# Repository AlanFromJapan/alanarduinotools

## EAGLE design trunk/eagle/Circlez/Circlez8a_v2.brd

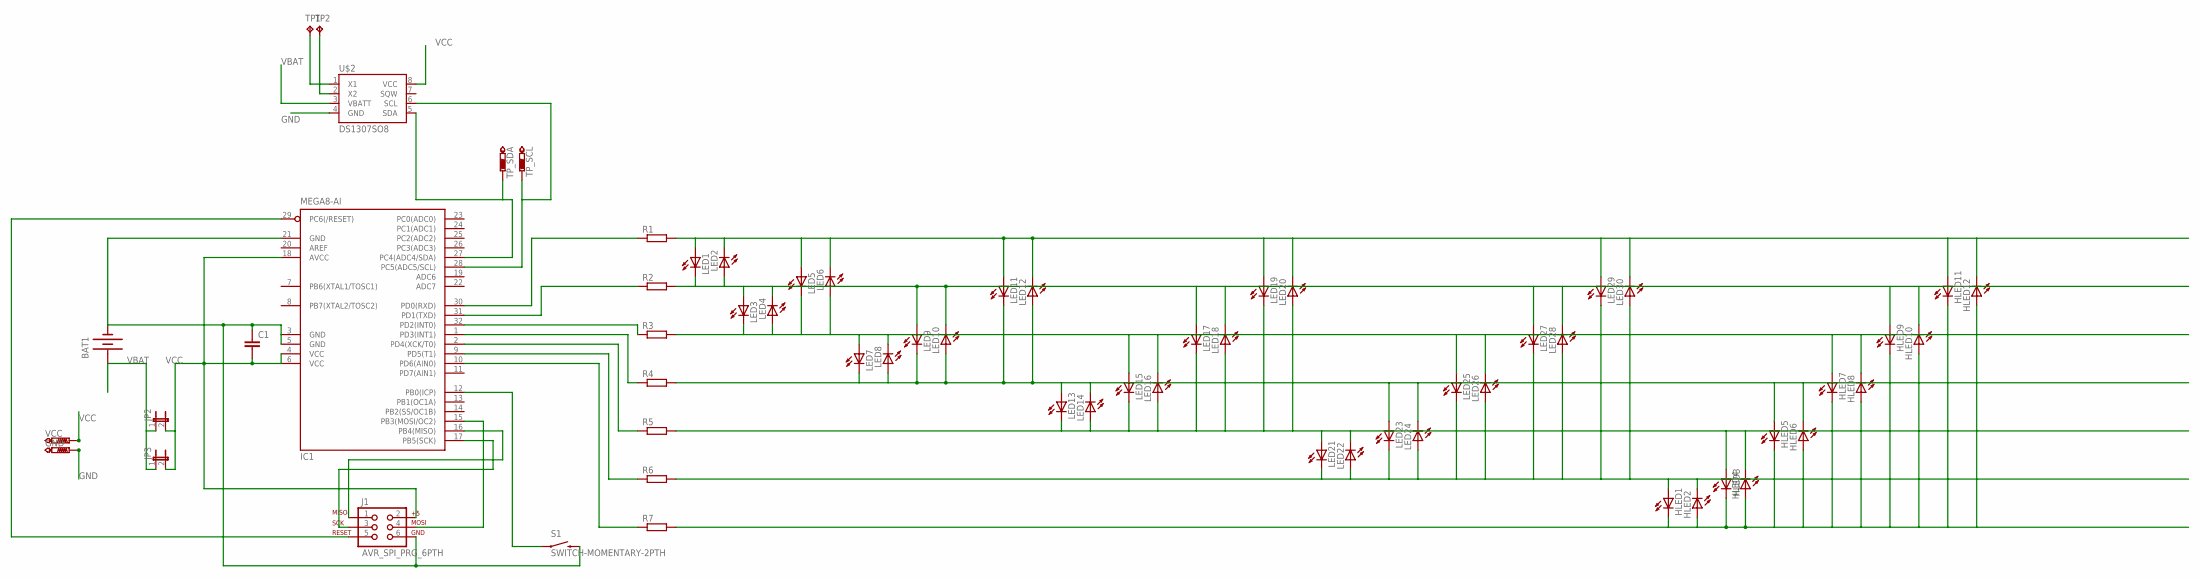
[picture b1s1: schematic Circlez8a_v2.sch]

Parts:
BAT1: BATTERY20PTH; BATTCOM_20MM_PTH
C1: C-EU025-024X044; C025-024X044
GND: PTR1TP15SQ; TP15SQ
HLED1, HLED2, HLED3, HLED4, HLED5, HLED6, HLED7, HLED8, HLED9, HLED10, HLED11, HLED12: LEDCHIP-LED0603; CHIP-LED0603
IC1: MEGA8-AI; TQFP32-08
J1: AVR_SPI_PRG_6PTH; 2X3
JP2: JUMPER-2SMD-NO; SJ_2S-NO
JP3: JUMPER-2PTH; 1X02
LED1, LED2, LED3, LED4, LED5, LED6, LED7, LED8, LED9, LED10, LED11, LED12, LED13, LED14, LED15, LED16, LED17, LED18, LED19, LED20, LED21, LED22, LED23, LED24, LED25, LED26, LED27, LED28, LED29, LED30: LEDCHIPLED_0603; CHIPLED_0603
R1, R2, R3, R4, R5, R6, R7: R-EU_R1206; R1206
S1: SWITCH-MOMENTARY-2PTH; TACTILE-PTH
TP1, TP2: TPTP13SQ; TP13SQ
TP_SCL: PTR1TP09SQ; TP09SQ
TP_SDA: PTR1TP09SQ; TP09SQ
U$2: DS1307SO8; SO08
VCC: PTR1TP15SQ; TP15SQ

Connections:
GND: BAT1.2 (-), C1.1, GND.TP, IC1.3 (GND), IC1.5 (GND), IC1.21 (GND), J1.6, S1.3 (2), U$2.4 (GND)
unnamed: IC1.12 (PB0(ICP)), S1.1
unnamed: HLED11.A, HLED12.C, LED1.A, LED2.C, LED5.A, LED6.C, LED11.A, LED12.C, LED19.A, LED20.C, LED29.A, LED30.C, R1.2
unnamed: IC1.16 (PB4(MISO)), J1.1
unnamed: IC1.17 (PB5(SCK)), J1.3
unnamed: IC1.15 (PB3(MOSI/OC2)), J1.4
unnamed: IC1.29 (PC6(/RESET)), J1.5
unnamed: HLED9.A, HLED10.C, LED1.C, LED2.A, LED3.A, LED4.C, LED9.A, LED10.C, LED17.A, LED18.C, LED27.A, LED28.C, R2.2
unnamed: HLED7.A, HLED8.C, LED3.C, LED4.A, LED5.C, LED6.A, LED7.A, LED8.C, LED15.A, LED16.C, LED25.A, LED26.C, R3.2
unnamed: HLED5.A, HLED6.C, LED7.C, LED8.A, LED9.C, LED10.A, LED11.C, LED12.A, LED13.A, LED14.C, LED23.A, LED24.C, R4.2
unnamed: HLED3.A, HLED4.C, LED13.C, LED14.A, LED15.C, LED16.A, LED17.C, LED18.A, LED19.C, LED20.A, LED21.A, LED22.C, R5.2
unnamed: IC1.28 (PC5(ADC5/SCL)), TP_SCL.TP, U$2.6 (SCL)
unnamed: HLED1.A, HLED2.C, LED21.C, LED22.A, LED23.C, LED24.A, LED25.C, LED26.A, LED27.C, LED28.A, LED29.C, LED30.A, R6.2
unnamed: HLED1.C, HLED2.A, HLED3.C, HLED4.A, HLED5.C, HLED6.A, HLED7.C, HLED8.A, HLED9.C, HLED10.A, HLED11.C, HLED12.A, R7.2
unnamed: IC1.30 (PD0(RXD)), R1.1
unnamed: IC1.31 (PD1(TXD)), R2.1
unnamed: IC1.32 (PD2(INT0)), R3.1
unnamed: IC1.1 (PD3(INT1)), R4.1
unnamed: IC1.2 (PD4(XCK/T0)), R5.1
unnamed: IC1.9 (PD5(T1)), R6.1
unnamed: IC1.10 (PD6(AIN0)), R7.1
unnamed: TP1.TP, U$2.1 (X1)
unnamed: TP2.TP, U$2.2 (X2)
unnamed: IC1.27 (PC4(ADC4/SDA)), TP_SDA.TP, U$2.5 (SDA)
VBAT: BAT1.1 (+), JP2.1, JP3.1, U$2.3 (VBATT)
VCC: C1.2, IC1.4 (VCC), IC1.6 (VCC), IC1.18 (AVCC), J1.2, JP2.2, JP3.2, U$2.8 (VCC), VCC.TP

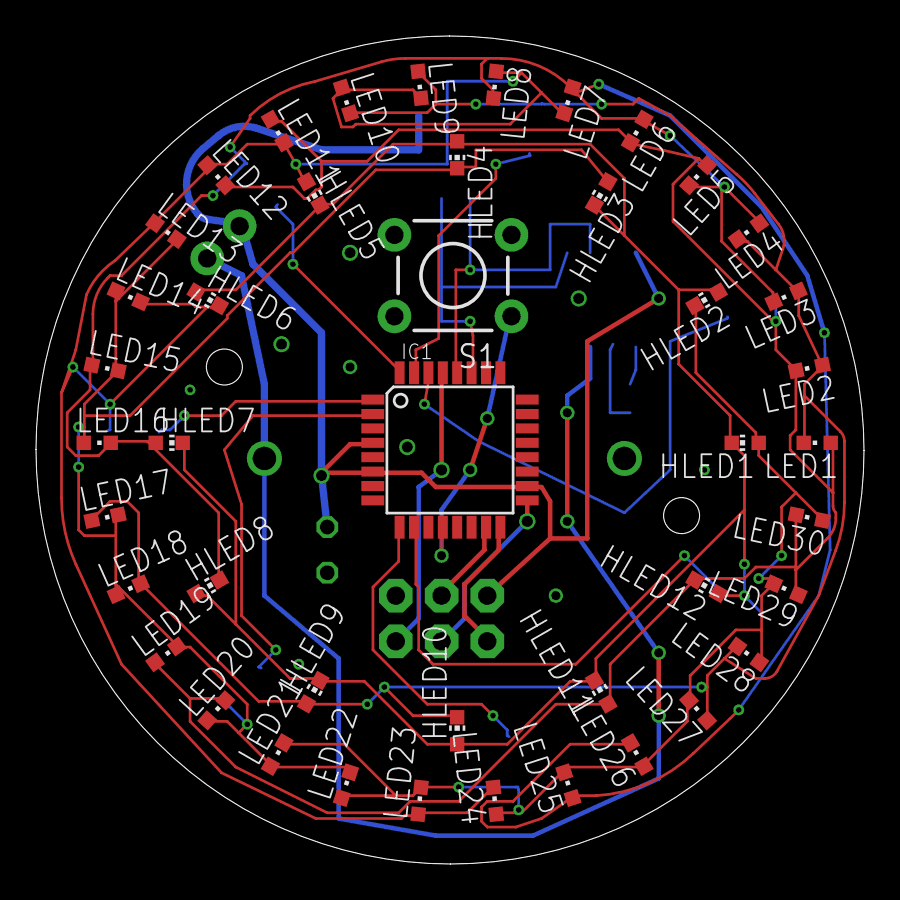
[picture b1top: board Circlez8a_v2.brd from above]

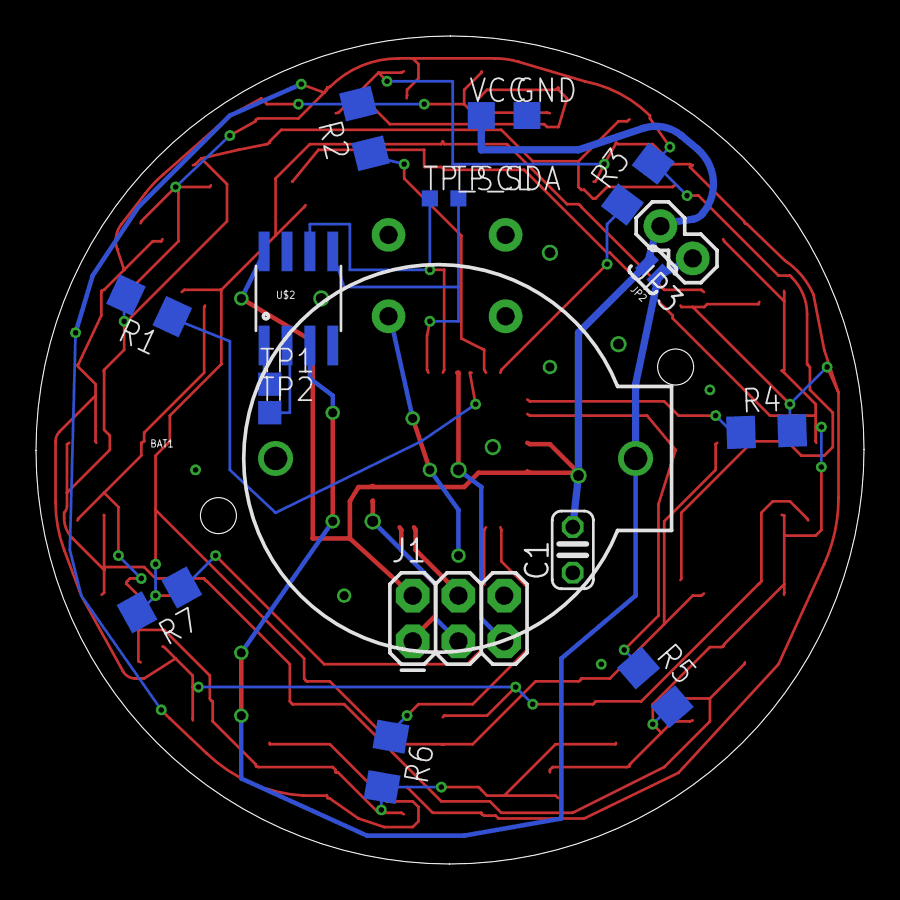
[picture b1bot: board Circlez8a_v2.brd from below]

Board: 4 copper layers, 46.0 x 46.0 mm, 63 parts (19 on the bottom side), 26 nets.

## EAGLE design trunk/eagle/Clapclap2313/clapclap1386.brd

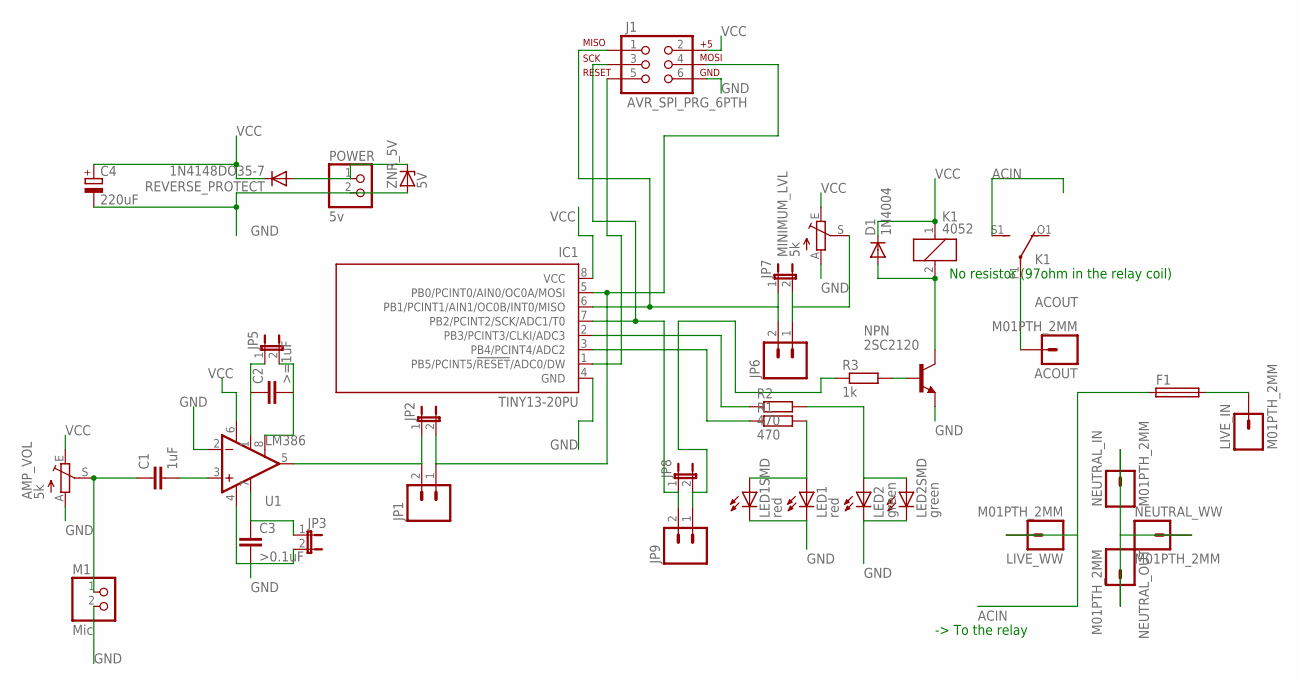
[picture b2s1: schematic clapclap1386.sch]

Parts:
ACOUT: M01PTH_2MM; 1X01_2MM
AMP_VOL: 5k; CT6
C1: 1uF; C050-024X044
C2: >=1uF; C050-024X044
C3: >0.1uF; C025-025X050
C4: 220uF; E2,5-6E
D1: 1N4004; DO41-10
F1: TE5
IC1: TINY13-20PU; DIL08
J1: AVR_SPI_PRG_6PTH; 2X3
JP1, JP6, JP9: M02PTH; 1X02
JP2, JP3, JP5, JP7, JP8: JUMPER-2SMD-NO; SJ_2S-NO
K1: 4052; F4052
LED1: red; LED3MM
LED1SMD: red; KA-3528ASYC
LED2: green; LED3MM
LED2SMD: green; KA-3528ASYC
LIVE_IN: M01PTH_2MM; 1X01_2MM
LIVE_WW: M01PTH_2MM; 1X01_2MM
M1: Mic; 1X02
MINIMUM_LVL: 5k; CT6
NEUTRAL_IN: M01PTH_2MM; 1X01_2MM
NEUTRAL_OUT: M01PTH_2MM; 1X01_2MM
NEUTRAL_WW: M01PTH_2MM; 1X01_2MM
NPN: 2SC2120; TO92-ECB
POWER: 5v; 1X02
R1, R2: 470; 0204V
R3: 1k; 0207/2V
REVERSE_PROTECT: 1N4148DO35-7; DO35-7
U1: LM386; DIP08
ZNR_5V: 5V; ZDIO-2.5

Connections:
ACIN: F1.1, K1.S1 (S), LIVE_WW.1
ACOUT: ACOUT.1, K1.P1
GND: AMP_VOL.A, C3.2, C4.-, IC1.4 (GND), J1.6, JP3.2, LED1.K (C), LED1SMD.C, LED2.K (C), LED2SMD.C, M1.2, MINIMUM_LVL.A, NPN.E, POWER.2, U1.2 (-IN), U1.4 (V-), ZNR_5V.A
unnamed: C1.2, U1.3 (+IN)
unnamed: AMP_VOL.S, C1.1, M1.1
unnamed: IC1.2 (PB3/PCINT3/CLKI/ADC3), R2.1
unnamed: C2.1, JP5.1, U1.1 (GAIN)
unnamed: IC1.3 (PB4/PCINT4/ADC2), R1.1
unnamed: LED1.A, LED1SMD.A, R1.2
unnamed: NPN.B, R3.2
unnamed: D1.A, K1.2, NPN.C
unnamed: IC1.5 (PB0/PCINT0/AIN0/OC0A/MOSI), J1.4, JP1.1, JP2.2
unnamed: LED2.A, LED2SMD.A, R2.2
unnamed: IC1.6 (PB1/PCINT1/AIN1/OC0B/INT0/MISO), J1.1, JP6.2, JP7.1
unnamed: NEUTRAL_IN.1, NEUTRAL_OUT.1, NEUTRAL_WW.1
unnamed: C2.2, JP5.2, U1.8 (GAIN)
unnamed: C3.1, JP3.1, U1.7 (BP)
unnamed: IC1.1 (PB5/PCINT5/!RESET!/ADC0/DW), J1.5
unnamed: JP1.2, JP2.1, U1.5 (OUT)
unnamed: POWER.1, REVERSE_PROTECT.A, ZNR_5V.C
unnamed: F1.2, LIVE_IN.1
unnamed: JP6.1, JP7.2, MINIMUM_LVL.S
unnamed: IC1.7 (PB2/PCINT2/SCK/ADC1/T0), J1.3, JP8.1, JP9.2
unnamed: JP8.2, JP9.1, R3.1
VCC: AMP_VOL.E, C4.+, D1.C, IC1.8 (VCC), J1.2, K1.1, MINIMUM_LVL.E, REVERSE_PROTECT.C, U1.6 (V+)

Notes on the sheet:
No resistor (97ohm in the relay coil)
-> To the relay

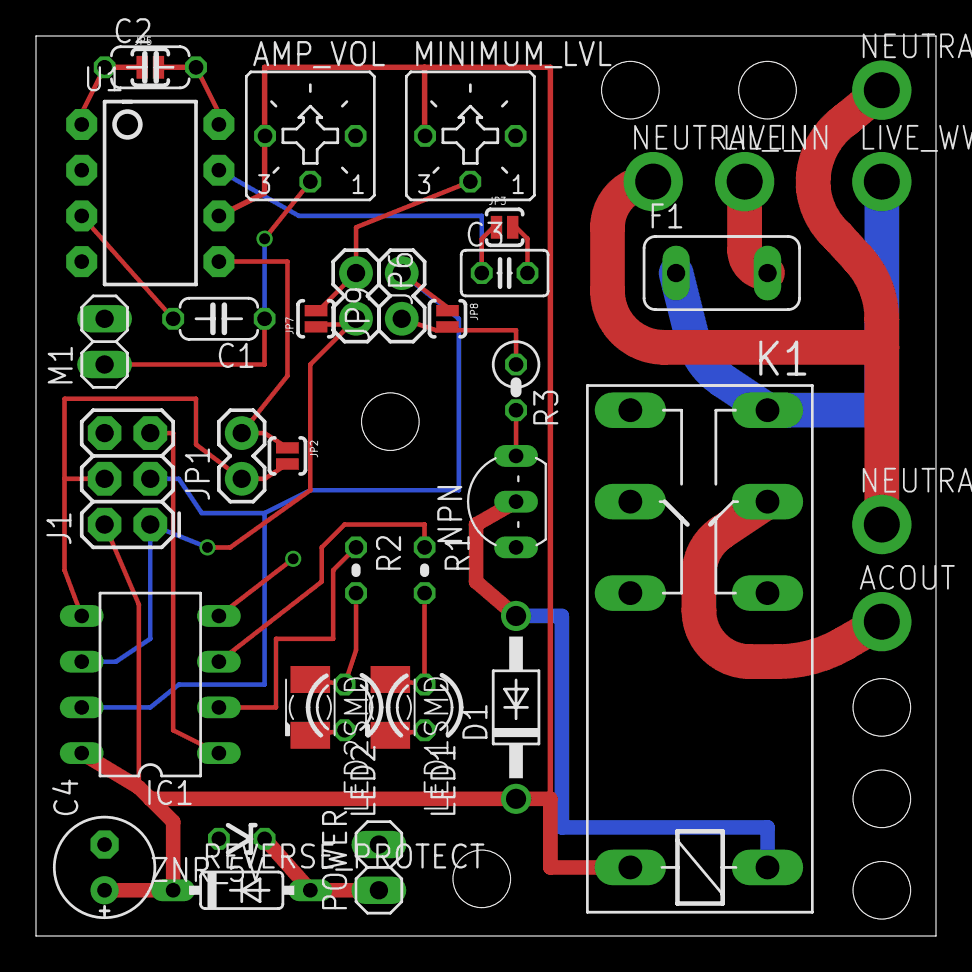
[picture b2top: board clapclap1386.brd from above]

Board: 4 copper layers, 50.0 x 50.0 mm, 38 parts (0 on the bottom side), 25 nets.

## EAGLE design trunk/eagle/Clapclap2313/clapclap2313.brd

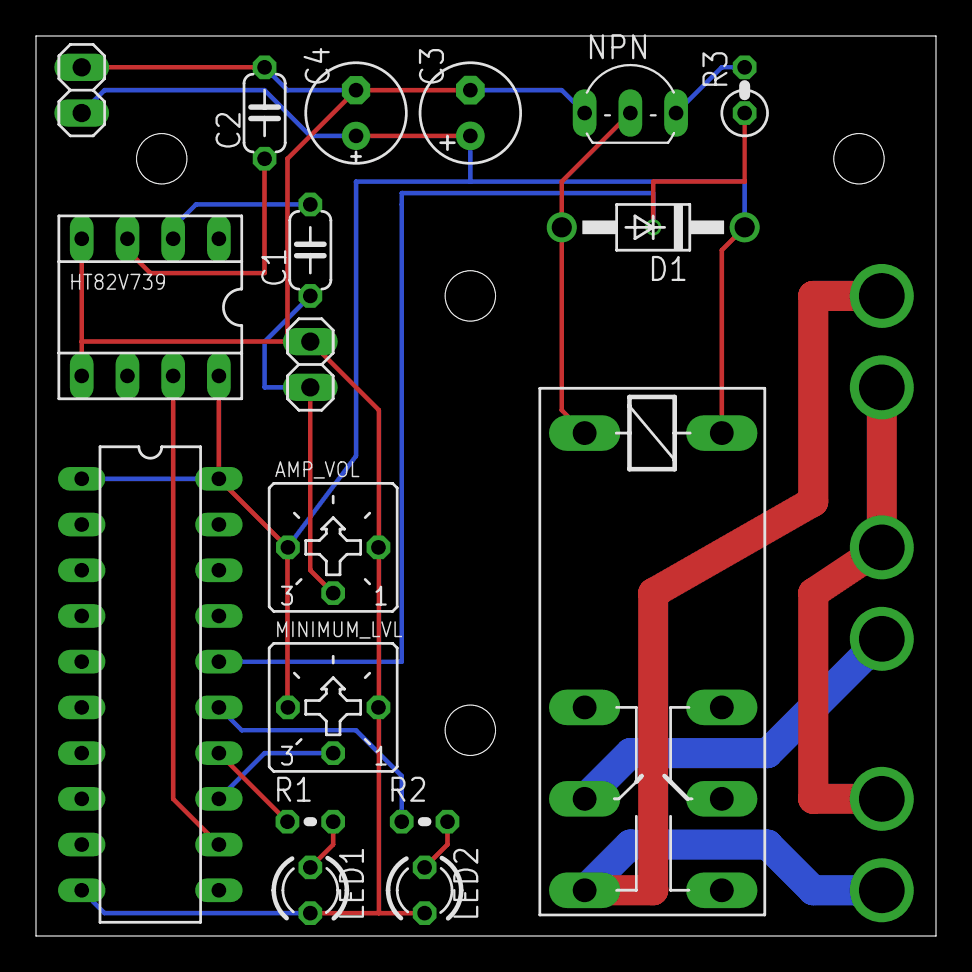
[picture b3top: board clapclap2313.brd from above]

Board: 2 copper layers, 50.0 x 50.0 mm, 24 parts (0 on the bottom side), 17 nets.

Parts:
ACOUT: SPECIAL_DRILL_0.1000; PAD_0.1000
AMP_VOL: 5k; CT6
ATTINY2313: AT90S2313P; DIL20
C1, C2: 1uF; C050-024X044
C3: 47uF; E2,5-6
C4: 220uF; E2,5-6E
D1: 1N4004; DO41-10
HT82V739: SOCKET-08
K1: 4052; F4052
LED1: red; LED3MM
LED2: green; LED3MM
LIVE_IN: SPECIAL_DRILL_0.1000; PAD_0.1000
LIVE_WW: SPECIAL_DRILL_0.1000; PAD_0.1000
M1: Mic; 1X02
MINIMUM_LVL: 5k; CT6
NEUTRAL_IN: SPECIAL_DRILL_0.1000; PAD_0.1000
NEUTRAL_OUT: SPECIAL_DRILL_0.1000; PAD_0.1000
NEUTRAL_WW: SPECIAL_DRILL_0.1000; PAD_0.1000
NPN: 2SC2120; TO92-ECB
POWER: 5v; 1X02
R1, R2: 470; 0204V
R3: 1k; 0207/2V

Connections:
ACIN: K1.S1, LIVE_IN.1, LIVE_WW.1
ACOUT: ACOUT.1, K1.P1
GND: AMP_VOL.A, ATTINY2313.10, C2.2, C3.-, C4.-, HT82V739.4, HT82V739.5, LED1.K, LED2.K, M1.2, MINIMUM_LVL.A, NPN.E, POWER.2
unnamed: C2.1, HT82V739.3
unnamed: ATTINY2313.16, R3.1
unnamed: AMP_VOL.S, C1.1, M1.1
unnamed: ATTINY2313.14, R1.1
unnamed: C1.2, HT82V739.2
unnamed: ATTINY2313.15, R2.1
unnamed: LED1.A, R1.2
unnamed: NPN.B, R3.2
unnamed: D1.A, K1.2, NPN.C
unnamed: ATTINY2313.12, HT82V739.7
unnamed: LED2.A, R2.2
unnamed: ATTINY2313.13, MINIMUM_LVL.S
unnamed: NEUTRAL_IN.1, NEUTRAL_OUT.1, NEUTRAL_WW.1
VCC: AMP_VOL.E, ATTINY2313.1, ATTINY2313.20, C3.+, C4.+, D1.C, HT82V739.8, K1.1, MINIMUM_LVL.E, POWER.1

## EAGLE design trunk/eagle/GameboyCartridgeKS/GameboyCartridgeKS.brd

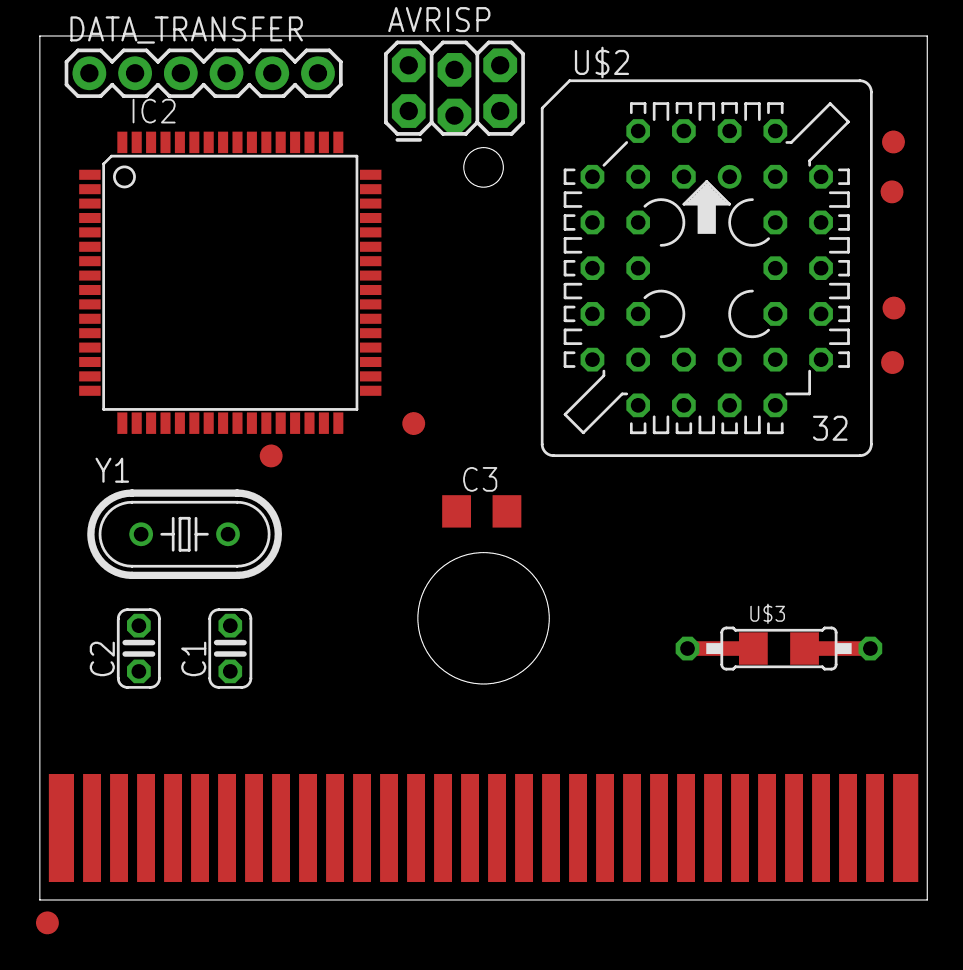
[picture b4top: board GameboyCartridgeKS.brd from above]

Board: 2 copper layers, 49.3 x 48.0 mm, 17 parts (0 on the bottom side), 21 nets.

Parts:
AVRISP: AVR_SPI_PRG_62X3_LOCK; 2X3_LOCK
C1, C2: 22pF; C025-024X044
C3: 10uF; C1206
DATA_TRANSFER: 1X06
IC2: MEGA64-A; TQFP64
PEN: TEST-POINT3X5; PAD.03X.05
TP1, TP2, TP3, TP4, TP5, TP6: TEST-POINT3X5; PAD.03X.05
U$1: CONNECTOR
U$2: EN29F002T; PLCC-S32
U$3: RESISTOR_COMBO1206; 207-10_SMD_COMBO
Y1: 16MHz max; HC49U-V

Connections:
22: IC2.51, U$1.22, U$2.13
23: IC2.50, U$1.23, U$2.14
24: IC2.49, U$1.24, U$2.15
25: IC2.48, U$1.25, U$2.17
26: IC2.47, U$1.26, U$2.18
27: IC2.46, U$1.27, U$2.19
28: IC2.45, U$1.28, U$2.20
29: IC2.44, U$1.29, U$2.21
!CE: TP1.P$1, U$1.21, U$2.22
!OE: TP2.P$1, U$1.4, U$2.24
!RESET: TP4.P$1, U$2.1
!WE: TP3.P$1, U$1.31, U$2.31, U$3.1, U$3.4
GND: AVRISP.6, C1.1, C2.1, C3.2, DATA_TRANSFER.1, IC2.22, IC2.53, IC2.63, TP6.P$1, U$1.32, U$2.16
MISO_TX: AVRISP.1, DATA_TRANSFER.5, IC2.3
MOSI_RX: AVRISP.4, DATA_TRANSFER.4, IC2.2
unnamed: C1.2, IC2.23, Y1.2
unnamed: AVRISP.5, IC2.20
unnamed: C2.2, IC2.24, Y1.1
PEN: IC2.1, PEN.P$1
SCK: AVRISP.3, IC2.11
VCC: AVRISP.2, C3.1, DATA_TRANSFER.3, IC2.21, IC2.52, IC2.62, IC2.64, TP5.P$1, U$2.32, U$3.2, U$3.3

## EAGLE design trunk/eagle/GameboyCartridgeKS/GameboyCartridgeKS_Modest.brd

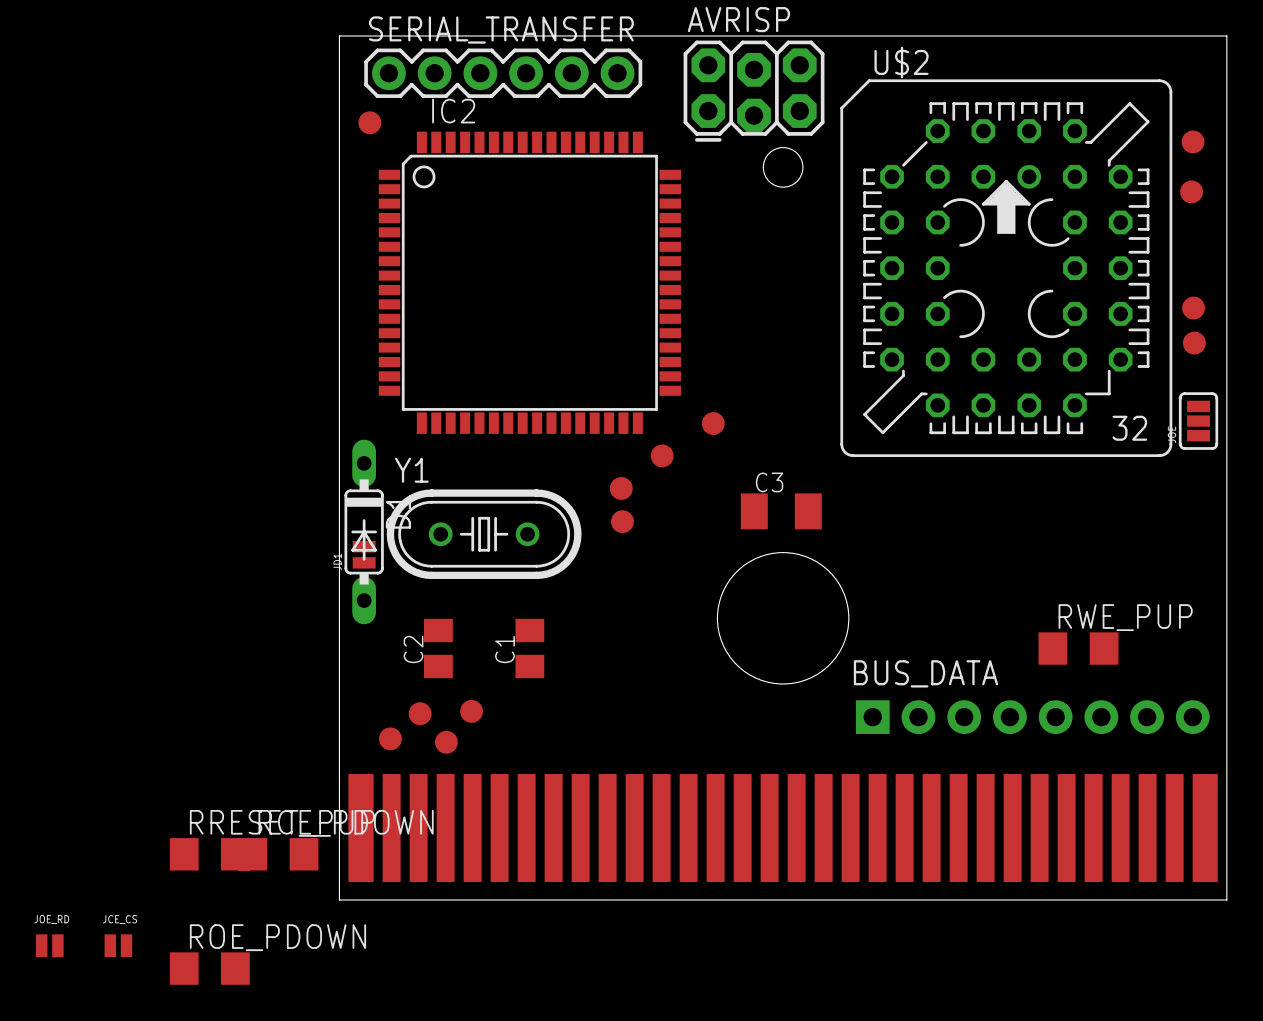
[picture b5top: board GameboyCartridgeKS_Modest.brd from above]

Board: 2 copper layers, 49.3 x 48.0 mm, 32 parts (0 on the bottom side), 49 nets.

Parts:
AVRISP: AVR_SPI_PRG_62X3_LOCK; 2X3_LOCK
BUS_DATA: 1X08_PIN1_NO_SILK
C1, C2: 22pF; C0805K
C3: 10uF; C1206K
D1: Germ.; DO35-7
IC2: MEGA64-A; TQFP64
JCE_CS: PAD-JUMPER-2-NO_NO_SILK
JD1: PAD-JUMPER-2-NO_NO_SILK
JOE: PAD-JUMPER-3-NO_YES_SILK
JOE_RD: PAD-JUMPER-2-NO_NO_SILK
PEN: TEST-POINT3X5; PAD.03X.05
RCE_PDOWN: R1206
ROE_PDOWN: R1206
RRESET_PUP: R1206
RWE_PUP: R1206
SCL, SCL1, SCL2, SCL3, SCL4: PAD.03X.05
SDA: PAD.03X.05
SERIAL_TRANSFER: 1X06
TP1, TP2, TP3, TP4, TP5, TP6: PAD.03X.05
U$1: CONNECTOR
U$2: EN29F002T; PLCC-S32
Y1: 16MHz max; HC49U-V

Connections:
22: BUS_DATA.1, IC2.51, U$1.22, U$2.13
23: BUS_DATA.2, IC2.50, U$1.23, U$2.14
24: BUS_DATA.3, IC2.49, U$1.24, U$2.15
25: BUS_DATA.4, IC2.48, U$1.25, U$2.17
26: BUS_DATA.5, IC2.47, U$1.26, U$2.18
27: BUS_DATA.6, IC2.46, U$1.27, U$2.19
28: BUS_DATA.7, IC2.45, U$1.28, U$2.20
29: BUS_DATA.8, IC2.44, U$1.29, U$2.21
!CE: IC2.13, JCE_CS.2, RCE_PDOWN.2, TP1.P$1, U$2.22
!GB_CS: IC2.30, JCE_CS.1, SCL4.P$1, U$1.5
!GB_RD: IC2.29, JOE.3, JOE_RD.1, SCL3.P$1, U$1.4
!GB_RESET: IC2.31, U$1.30
!GB_WR: IC2.28, SCL2.P$1, U$1.3
!OE: JOE.2, JOE_RD.2, ROE_PDOWN.2, TP2.P$1, U$2.24
!RESET: IC2.16, RRESET_PUP.1, TP4.P$1, U$2.1
!WE: IC2.15, RWE_PUP.1, TP3.P$1, U$2.31
ADDRESS0: IC2.61, U$1.6, U$2.12
ADDRESS1: IC2.60, U$1.7, U$2.11
ADDRESS2: IC2.59, U$1.8, U$2.10
ADDRESS3: IC2.58, U$1.9, U$2.9
ADDRESS4: IC2.57, U$1.10, U$2.8
ADDRESS5: IC2.56, U$1.11, U$2.7
ADDRESS6: IC2.55, U$1.12, U$2.6
ADDRESS7: IC2.54, U$1.13, U$2.5
ADDRESS8: IC2.35, U$1.14, U$2.27
ADDRESS9: IC2.36, U$1.15, U$2.26
ADDRESS10: IC2.37, U$1.16, U$2.23
ADDRESS11: IC2.38, U$1.17, U$2.25
ADDRESS12: IC2.39, U$1.18, U$2.4
ADDRESS13: IC2.40, U$1.19, U$2.28
ADDRESS14: IC2.41, U$1.20, U$2.29
ADDRESS15: IC2.42, U$1.21, U$2.3
ADDRESS16: IC2.8, U$2.2
ADDRESS17: IC2.9, U$2.30
GB_CLOCK: IC2.27, SCL1.P$1, U$1.2
GB_MIC_IN: IC2.17, U$1.31
GND: AVRISP.6, C1.1, C2.1, C3.2, IC2.22, IC2.53, IC2.63, RCE_PDOWN.1, ROE_PDOWN.1, SERIAL_TRANSFER.1, TP6.P$1, U$1.32, U$2.16
MISO_TX: AVRISP.1, IC2.3, SERIAL_TRANSFER.5
MOSI_RX: AVRISP.4, IC2.2, SERIAL_TRANSFER.4
unnamed: IC2.26, SDA.P$1
unnamed: C1.2, IC2.23, Y1.2
unnamed: AVRISP.5, IC2.20
unnamed: C2.2, IC2.24, Y1.1
unnamed: IC2.25, SCL.P$1
unnamed: IC2.14, JOE.1
PEN: IC2.1, PEN.P$1
SCK: AVRISP.3, IC2.11
VCC: AVRISP.2, C3.1, D1.C, IC2.21, IC2.52, IC2.62, IC2.64, JD1.2, RRESET_PUP.2, RWE_PUP.2, SERIAL_TRANSFER.3, TP5.P$1, U$2.32
VDD: D1.A, JD1.1, U$1.1

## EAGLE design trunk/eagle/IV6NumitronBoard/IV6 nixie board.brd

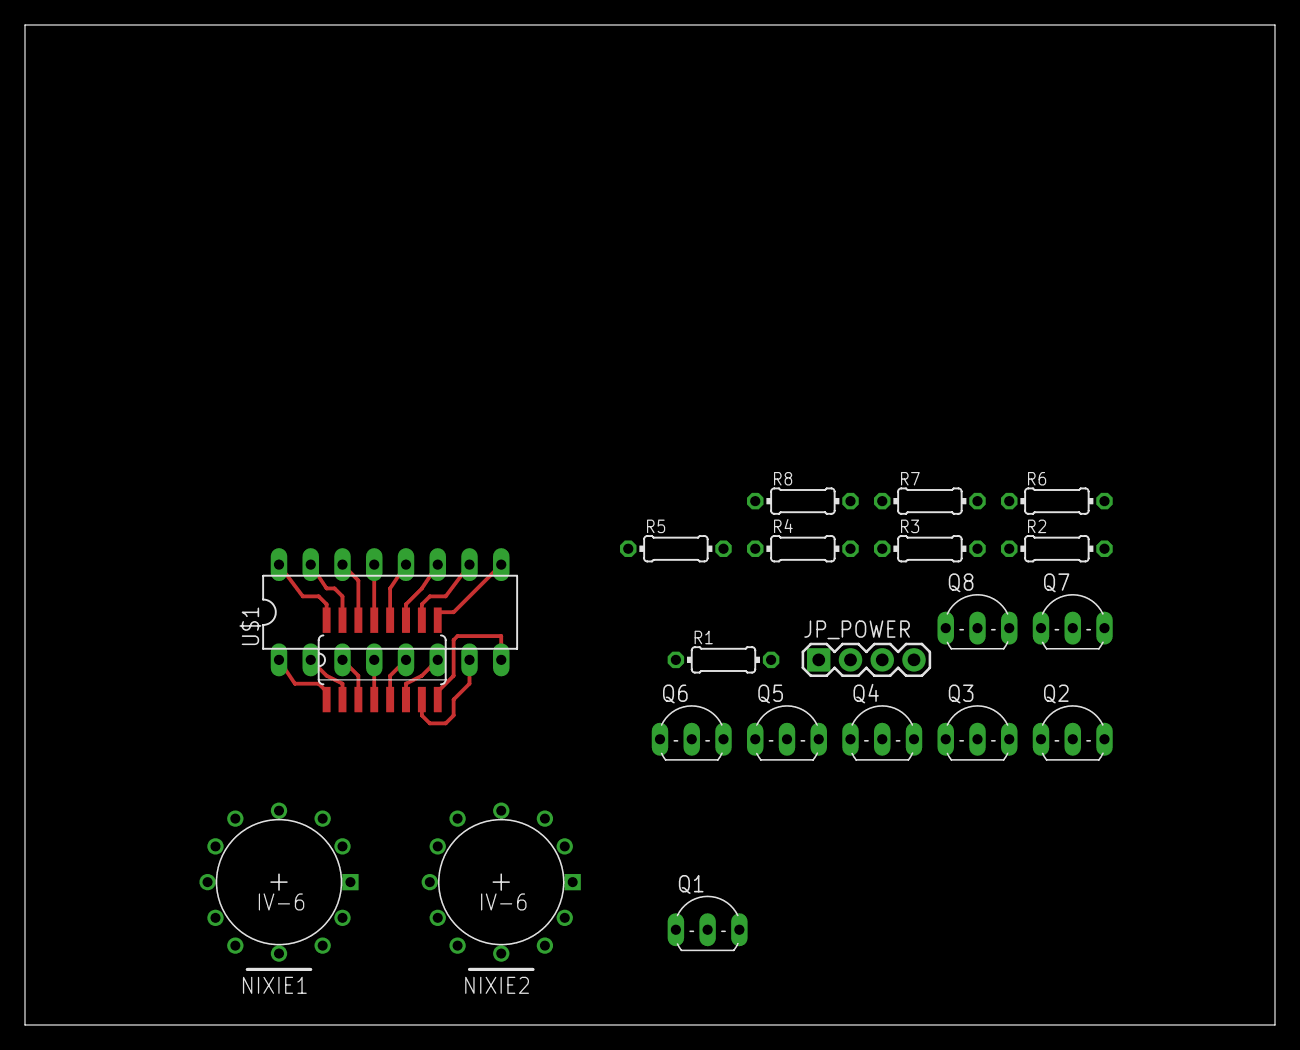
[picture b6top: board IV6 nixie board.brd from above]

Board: 2 copper layers, 100.0 x 80.0 mm, 20 parts (0 on the bottom side), 29 nets, no tracks yet.

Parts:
JP_POWER: 1X04
NIXIE1, NIXIE2: IV6_NUMITRONLARGE; IV6_NUMITRON_PAC_LARGE
Q1, Q2, Q3, Q4, Q5, Q6, Q7, Q8: BC449; TO92-EBC
R1, R2, R3, R4, R5, R6, R7, R8: 0204/7
U$1: 74HC595_SMDDIP_COMBOTHINPAD; DIL16_SO16_PAC2

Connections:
GND: JP_POWER.1, NIXIE1.FIL_M, NIXIE2.FIL_M, U$1.8, U$1.S8
unnamed: NIXIE1.BOT, NIXIE2.BOT, Q1.E
unnamed: NIXIE1.DOT, NIXIE2.DOT, Q2.E
unnamed: NIXIE1.BR, NIXIE2.BR, Q3.E
unnamed: NIXIE1.BL, NIXIE2.BL, Q4.E
unnamed: NIXIE1.MID, NIXIE2.MID, Q5.E
unnamed: NIXIE1.TL, NIXIE2.TL, Q6.E
unnamed: NIXIE1.TR, NIXIE2.TR, Q7.E
unnamed: NIXIE1.TOP, NIXIE2.TOP, Q8.E
unnamed: NIXIE1.NC, NIXIE2.NC
unnamed: R1.1, U$1.15, U$1.S15
unnamed: Q1.B, R1.2
unnamed: R2.1, U$1.1, U$1.S1
unnamed: Q2.B, R2.2
unnamed: R3.1, U$1.2, U$1.S2
unnamed: Q3.B, R3.2
unnamed: R4.1, U$1.3, U$1.S3
unnamed: Q4.B, R4.2
unnamed: R5.1, U$1.4, U$1.S4
unnamed: Q5.B, R5.2
unnamed: R6.1, U$1.5, U$1.S5
unnamed: Q6.B, R6.2
unnamed: R7.1, U$1.6, U$1.S6
unnamed: Q7.B, R7.2
unnamed: R8.1, U$1.7, U$1.S7
unnamed: Q8.B, R8.2
VCC_1.5: JP_POWER.2, NIXIE1.FIL_P, NIXIE2.FIL_P
VCC_5: JP_POWER.3, U$1.16, U$1.S16
VCC_HI: JP_POWER.4, NIXIE1.GRID_P, NIXIE2.GRID_P, Q1.C, Q2.C, Q3.C, Q4.C, Q5.C, Q6.C, Q7.C, Q8.C

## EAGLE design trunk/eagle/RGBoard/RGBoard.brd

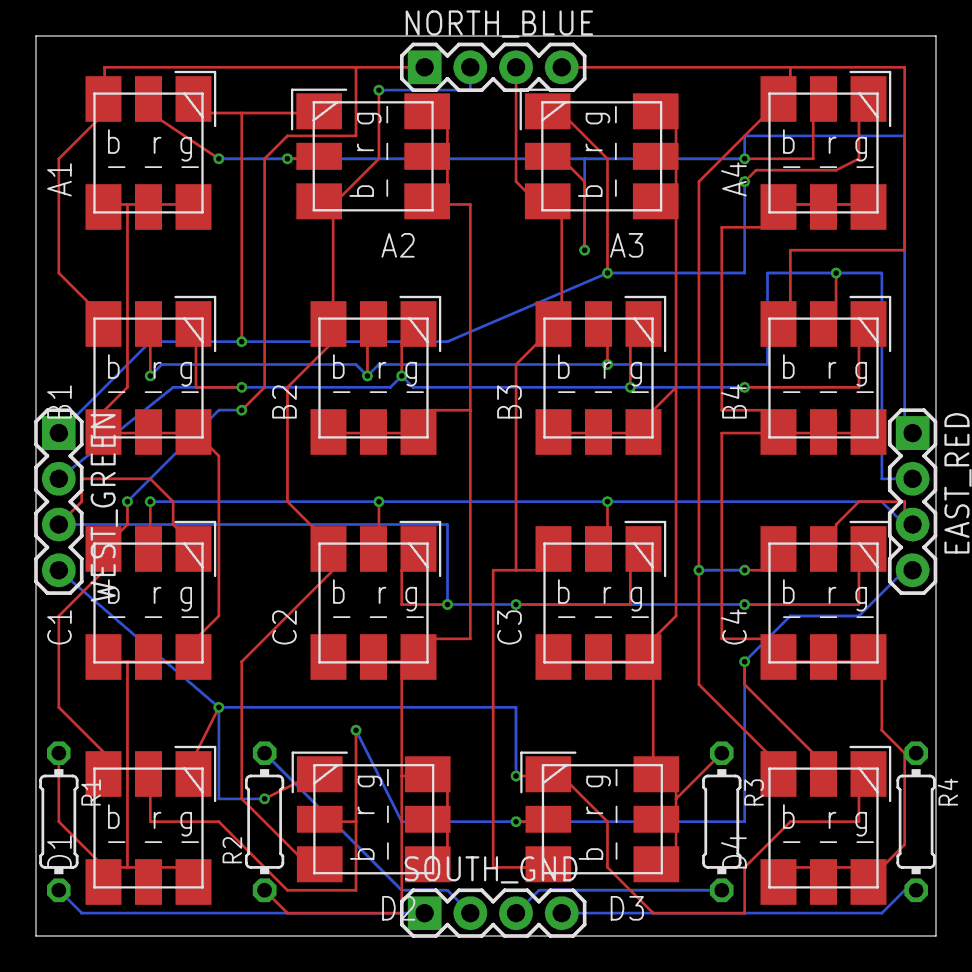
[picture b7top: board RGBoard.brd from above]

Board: 2 copper layers, 50.0 x 50.0 mm, 24 parts (0 on the bottom side), 20 nets.

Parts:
A1, A2, A3, A4: RGB-SMT-SQUARE; SMT-SQUARE6
B1, B2, B3, B4: RGB-SMT-SQUARE; SMT-SQUARE6
C1, C2, C3, C4: RGB-SMT-SQUARE; SMT-SQUARE6
D1, D2, D3, D4: RGB-SMT-SQUARE; SMT-SQUARE6
EAST_RED: 1X04
NORTH_BLUE: 1X04
R1, R2, R3, R4: 251; 0204/7
SOUTH_GND: 1X04
WEST_GREEN: 1X04

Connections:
GND1: A1.KB, A1.KG, A1.KR, B1.KB, B1.KG, B1.KR, C1.KB, C1.KG, C1.KR, D1.KB, D1.KG, D1.KR, R1.1
GND2: A2.KB, A2.KG, A2.KR, B2.KB, B2.KG, B2.KR, C2.KB, C2.KG, C2.KR, D2.KB, D2.KG, D2.KR, R2.1
GND3: A3.KB, A3.KG, A3.KR, B3.KB, B3.KG, B3.KR, C3.KB, C3.KG, C3.KR, D3.KB, D3.KG, D3.KR, R3.1
GND4: A4.KB, A4.KG, A4.KR, B4.KB, B4.KG, B4.KR, C4.KB, C4.KG, C4.KR, D4.KB, D4.KG, D4.KR, R4.1
unnamed: R1.2, SOUTH_GND.1
unnamed: R2.2, SOUTH_GND.2
unnamed: R3.2, SOUTH_GND.3
unnamed: R4.2, SOUTH_GND.4
unnamed: A1.AR, A2.AR, A3.AR, A4.AR, EAST_RED.1
unnamed: B1.AR, B2.AR, B3.AR, B4.AR, EAST_RED.2
unnamed: C1.AR, C2.AR, C3.AR, C4.AR, EAST_RED.3
unnamed: D1.AR, D2.AR, D3.AR, D4.AR, EAST_RED.4
unnamed: A1.AB, B1.AB, C1.AB, D1.AB, NORTH_BLUE.1
unnamed: A2.AB, B2.AB, C2.AB, D2.AB, NORTH_BLUE.2
unnamed: A3.AB, B3.AB, C3.AB, D3.AB, NORTH_BLUE.3
unnamed: A4.AB, B4.AB, C4.AB, D4.AB, NORTH_BLUE.4
unnamed: A1.AG, A2.AG, A3.AG, A4.AG, WEST_GREEN.1
unnamed: B1.AG, B2.AG, B3.AG, B4.AG, WEST_GREEN.2
unnamed: C1.AG, C2.AG, C3.AG, C4.AG, WEST_GREEN.3
unnamed: D1.AG, D2.AG, D3.AG, D4.AG, WEST_GREEN.4

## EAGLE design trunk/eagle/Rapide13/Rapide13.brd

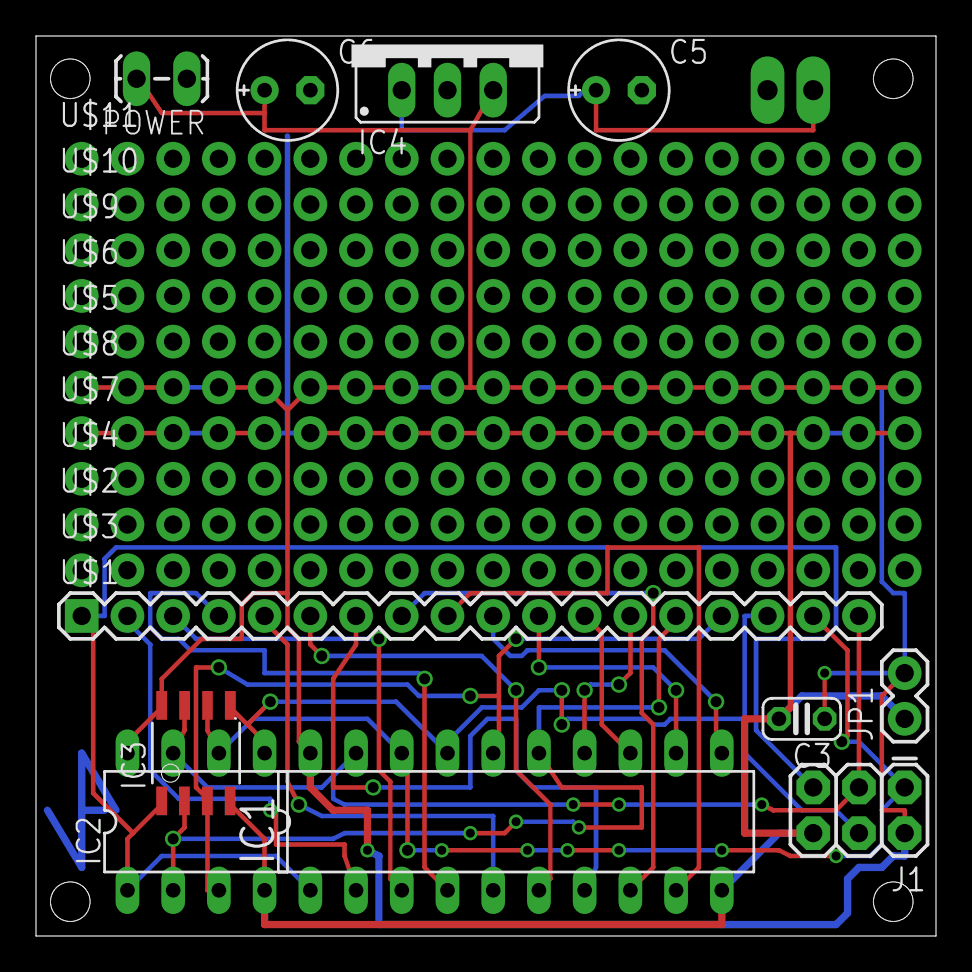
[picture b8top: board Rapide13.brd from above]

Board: 2 copper layers, 50.0 x 50.0 mm, 22 parts (0 on the bottom side), 21 nets.

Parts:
C3: C025-024X044
C5: 47u; E2,5-6E
C6: 4.7u; E2,5-6E
IC1: AT90S2313P; DIL20
IC2: TINY13-20PU; DIL08
IC3: TINY13-20SSU; 8S1
IC4: 78XXS
J1: AVR_SPI_PRG_6PTH; 2X3
JP1: 1X02
POWER: 1X02_LOCK_LONGPADS
U$1: M18_; 1X18
U$2, U$3, U$4, U$5, U$6, U$7, U$8, U$9, U$10, U$11: M191X19_NO_SILK; 1X19_NO_SILK
UNREGULATED: 1X02_LONGPADS

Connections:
GND: C3.2, C5.-, C6.-, IC1.10, IC2.4, IC3.4, IC4.GND, J1.6, JP1.1, POWER.1, U$7.1, U$7.2, U$7.3, U$7.4, U$7.5, U$7.6, U$7.7, U$7.8, U$7.9, U$7.10, U$7.11, U$7.12, U$7.13, U$7.14, U$7.15, U$7.16, U$7.17, U$7.18, U$7.19, UNREGULATED.1
MISO: IC1.18, IC2.6, IC3.6, J1.1, U$1.17
MOSI: IC1.17, IC2.5, IC3.5, J1.4, U$1.16
unnamed: IC1.4, U$1.4
unnamed: IC1.5, U$1.5
unnamed: IC1.2, U$1.2
unnamed: IC1.3, U$1.3
unnamed: IC1.6, U$1.6
unnamed: IC1.7, U$1.7
unnamed: IC1.8, U$1.8
unnamed: IC1.9, U$1.9
unnamed: IC1.11, U$1.10
unnamed: IC1.12, U$1.11
unnamed: IC1.13, U$1.12
unnamed: IC1.14, U$1.13
RESET: IC1.1, IC2.1, IC3.1, J1.5, U$1.1
SCK: IC1.19, IC2.7, IC3.7, J1.3, U$1.18
TINY13_B3: IC1.15, IC2.2, IC3.2, U$1.14
TINY13_B4: IC1.16, IC2.3, IC3.3, U$1.15
VCC: C3.1, C6.+, IC1.20, IC2.8, IC3.8, IC4.OUT, J1.2, JP1.2, POWER.2, U$8.1, U$8.2, U$8.3, U$8.4, U$8.5, U$8.6, U$8.7, U$8.8, U$8.9, U$8.10, U$8.11, U$8.12, U$8.13, U$8.14, U$8.15, U$8.16, U$8.17, U$8.18, U$8.19
VIN: C5.+, IC4.IN, UNREGULATED.2

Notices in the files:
parts and their libraries:
SparkFun: Licensing: CC v3.0 Share-Alike You are welcome to use this library for commercial purposes.
SparkFun-Connectors: Licensing: Creative Commons ShareAlike 4.0 International - https://creativecommons.org/licenses/by-sa/4.0
